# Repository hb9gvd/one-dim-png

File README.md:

# One Dim Pong
Arduino code and PCB Files, either Kicad and ready-to-order Gerber Files for One Dimensional Pong Game.
This repository exists for users to get files, open issues and make contributions.

To get started see [Firmware versions](#firmware-versions) part or look table of contents for more.

Table of contents
=================
* [Firmware versions](#firmware-versions)
* [Hardware schematic](#schematic)

Firmware Versions
============
To use with 100ms pulse coin counter 
[Arduino code and used libraries](./software/).

Schematic
============
Repository has updated Schematic made with Kicad. Some more information could be found 
[here](./hardware/kicad/).
Altough, find here printable 
[Schematic](./hardware/one-dim-pong.pdf) 
and have a look to the 
[PCB picture](./hardware/One-Dim-Pong-3D-V1.png).

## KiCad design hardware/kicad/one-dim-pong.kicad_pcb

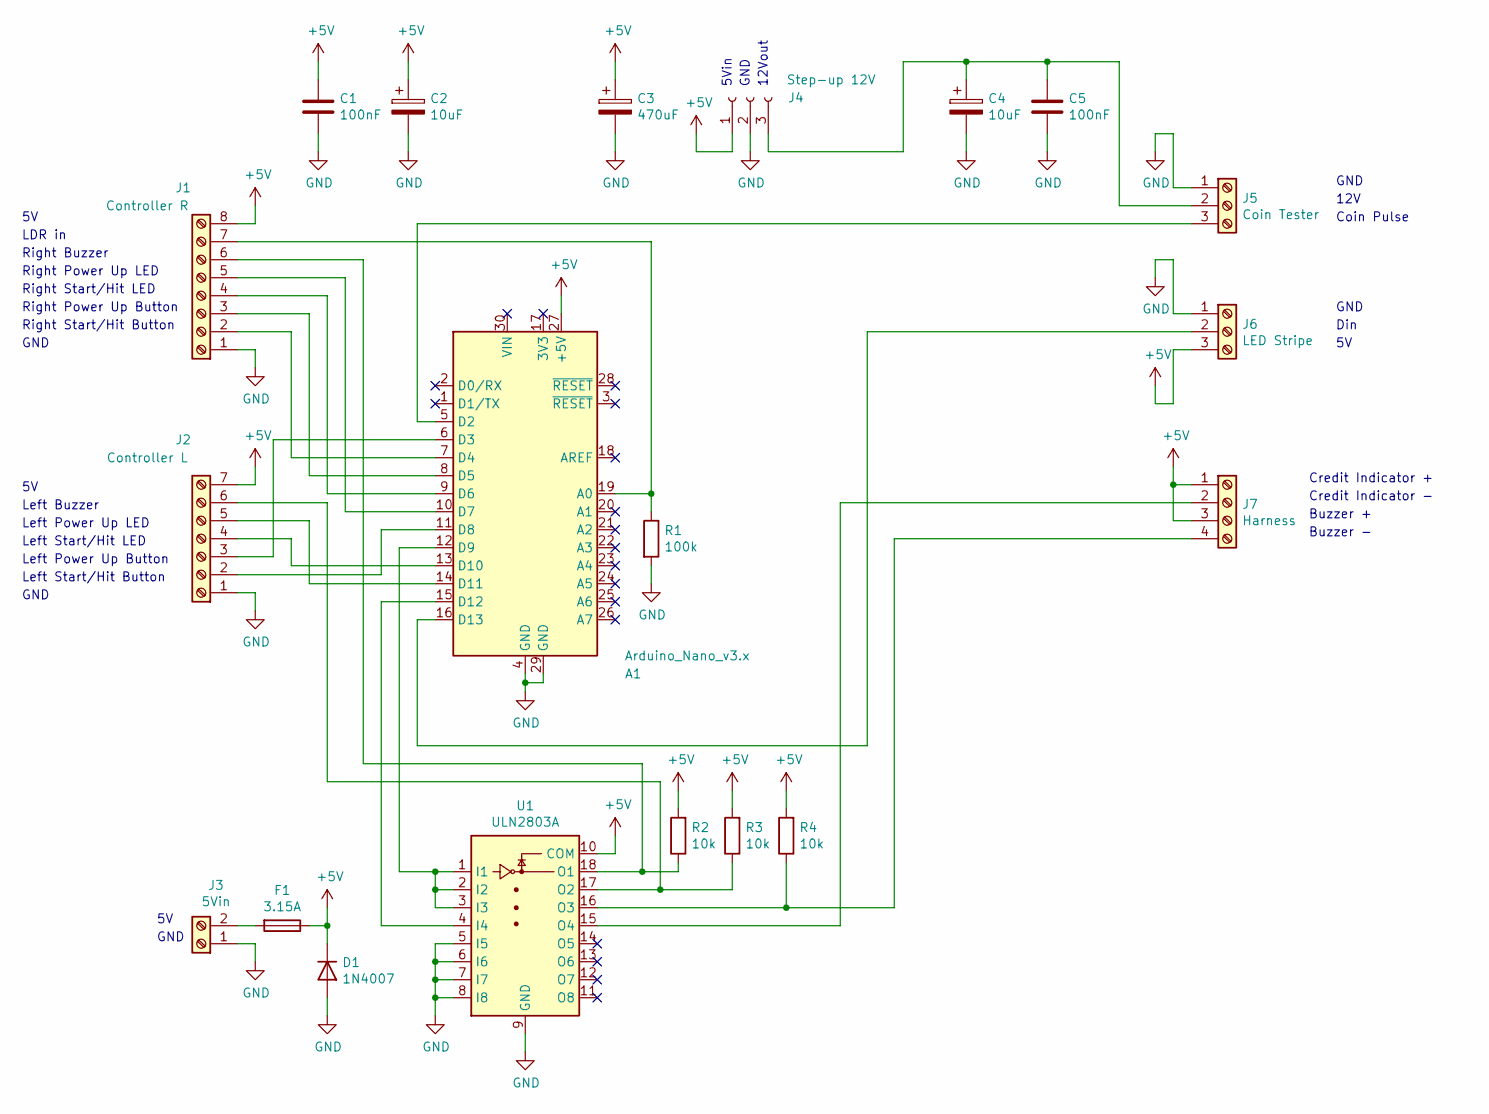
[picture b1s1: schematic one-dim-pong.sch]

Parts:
A1: Arduino_Nano_v3.x; Arduino_Nano
C1, C5: 100nF; C_Disc_D5.0mm_W2.5mm_P2.50mm
C2, C4: 10uF; CP_Radial_D10.0mm_P2.50mm_P5.00mm
C3: 470uF; CP_Radial_D10.0mm_P2.50mm_P5.00mm
D1: 1N4007; D_DO-15_P10.16mm_Horizontal
F1: 3.15A; Fuse_BelFuse_0ZRE0008FF_L8.3mm_W3.8mm
J1: Controller R; TerminalBlock_TE_282834-8_1x08_P2.54mm_Horizontal
J2: Controller L; TerminalBlock_TE_282834-7_1x07_P2.54mm_Horizontal
J3: 5Vin; TerminalBlock_Altech_AK300-2_P5.00mm
J4: Step-up 12V; PinHeader_1x03_P2.54mm_Vertical
J5: Coin Tester; TerminalBlock_TE_282834-3_1x03_P2.54mm_Horizontal
J6: LED Stripe; TerminalBlock_Altech_AK300-3_P5.00mm
J7: Harness; TerminalBlock_TE_282834-4_1x04_P2.54mm_Horizontal
R1: 100k; R_Axial_DIN0207_L6.3mm_D2.5mm_P10.16mm_Horizontal
R2, R3, R4: 10k; R_Axial_DIN0207_L6.3mm_D2.5mm_P10.16mm_Horizontal
U1: ULN2803A; DIP-18_W7.62mm_Socket_LongPads

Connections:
+5V: A1.27 (+5V), C1.1, C2.1, C3.1, D1.1 (K), F1.1, J1.8, J2.7, J4.1, J6.3, J7.1, J7.3, R2.2, R3.2, R4.2, U1.10 (COM)
GND: A1.4 (GND), A1.29 (GND), C1.2, C2.2, C3.2, C4.2, C5.2, D1.2 (A), J1.1, J2.1, J3.1, J4.2, J5.1, J6.1, R1.2, U1.5 (I5), U1.6 (I6), U1.7 (I7), U1.8 (I8), U1.9 (GND)
unnamed: A1.5 (D2), J5.3
unnamed: A1.6 (D3), J2.3
unnamed: A1.7 (D4), J1.2
unnamed: A1.8 (D5), J1.3
unnamed: A1.9 (D6), J1.4
unnamed: A1.10 (D7), J1.5
unnamed: A1.11 (D8), J2.2
unnamed: A1.12 (D9), U1.1 (I1), U1.2 (I2), U1.3 (I3)
unnamed: A1.13 (D10), J2.4
unnamed: A1.14 (D11), J2.5
unnamed: A1.15 (D12), U1.4 (I4)
unnamed: A1.16 (D13), J6.2
unnamed: A1.19 (A0), J1.7, R1.1
unnamed: C4.1, C5.1, J4.3, J5.2
unnamed: F1.2, J3.2
unnamed: J1.6, R2.1, U1.18 (O1)
unnamed: J2.6, R3.1, U1.17 (O2)
unnamed: J7.2, U1.15 (O4)
unnamed: J7.4, R4.1, U1.16 (O3)

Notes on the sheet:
Credit Indicator -
Credit Indicator +
Buzzer +
Buzzer -
5Vin
GND
12Vout
12V
Coin Pulse
Right Start/Hit Button
Right Power Up Button
Right Start/Hit LED
Right Power Up LED
Right Buzzer
LDR in
Left Start/Hit Button
Left Power Up Button
Left Start/Hit LED
Left Power Up LED
Left Buzzer
Din

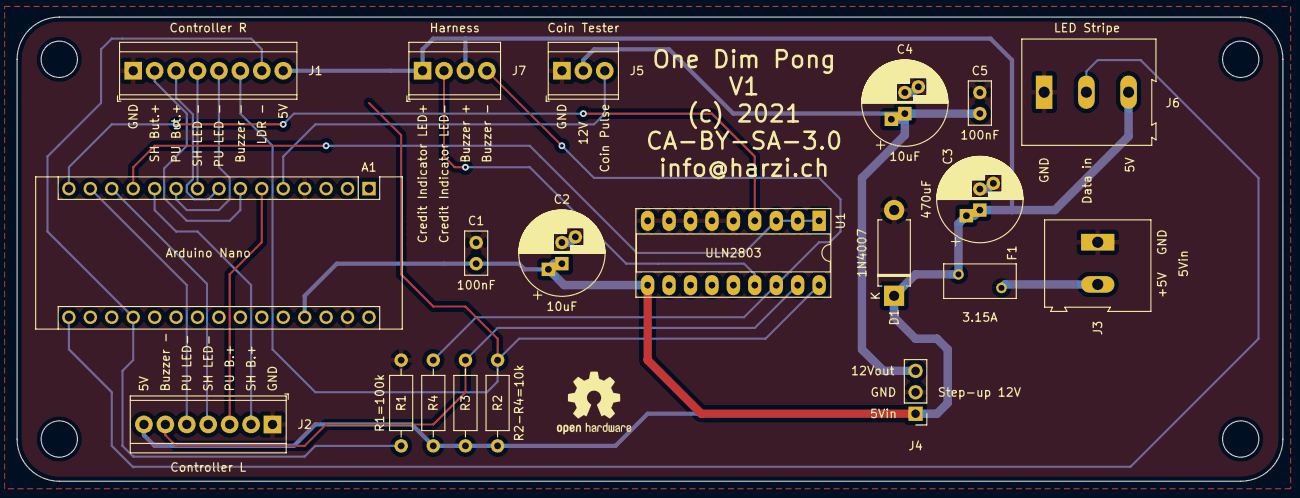
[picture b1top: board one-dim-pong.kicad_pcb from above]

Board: 2 copper layers, 150.0 x 55.0 mm, 20 parts (0 on the bottom side), 21 nets.

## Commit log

2021-11-12 added HW files
2021-11-12 added SW files
2021-11-12 changes to README.md
2021-11-12 changed paths in README.md to relative paths

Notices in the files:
hardware/kicad/one-dim-pong.kicad_pcb:
(c) 2021
